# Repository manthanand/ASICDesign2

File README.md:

# ASIC Design 2 - Validation of 128-Bit AES Core

## AES Test Board
This folder contains the KiCAD project files for the board that houses the testbench for the AES Core. It mates with a BASYS 3 ARTIX 7 FPGA Board that is used to stimulate the AES
core with input signals. The following is a list of the pins and what they connect to on the FPGA:
| BASYS 3 Board Pin | AES Core PIN | 
|-------------------|--------------|
|        JB1        |      CLK     |
|        JB2        |      SE      |
|        JB3        |      EN      |
|        JB4        |     KRDY     |
|        JB7        |      SI      |
|        JB8        |     SCLK     |
|        JB9        |      SU      |
|        JB10       |     RSTN     |
|        JC7        |     DRDY     |
|        JC8        |      SO      |
|        JC9        |      BSY     |

`AES Board J3`: The following pin is used to bypass the LDO output to allow for testing with different operating voltages. If jumpered, it will use the LDO output. In order to 
replace with a power supply, remove the jumper, place `V+` of the PSU on the bottom pin and `V-` of the PSU on the `VSS1` testpoint.

## AES Test & Emulation

This folder contains the Vivado project with the testbench and emulation project files. The project is structured such that both modules are in the same project, but one can 
be set as the top module and compiled into a bitstream. That way the same project can be used for both purposes. However, since the emulation did not work when separated onto 
2 boards, this project has now been centered around just the FPGA stimuli into the PCB.

## Scripts

During the course of our debugging, we realized that the scan chains within our core were reordered before tapeout. This meant that we had to parse through the final PNR Signoff
from last semester and recreate the verilog that we emulated this semester to accurately test our scan chain. This folder houses the scripts to automatically generate the verilog
that is necessary to reorder the scan chains for sending data in and out of the core.

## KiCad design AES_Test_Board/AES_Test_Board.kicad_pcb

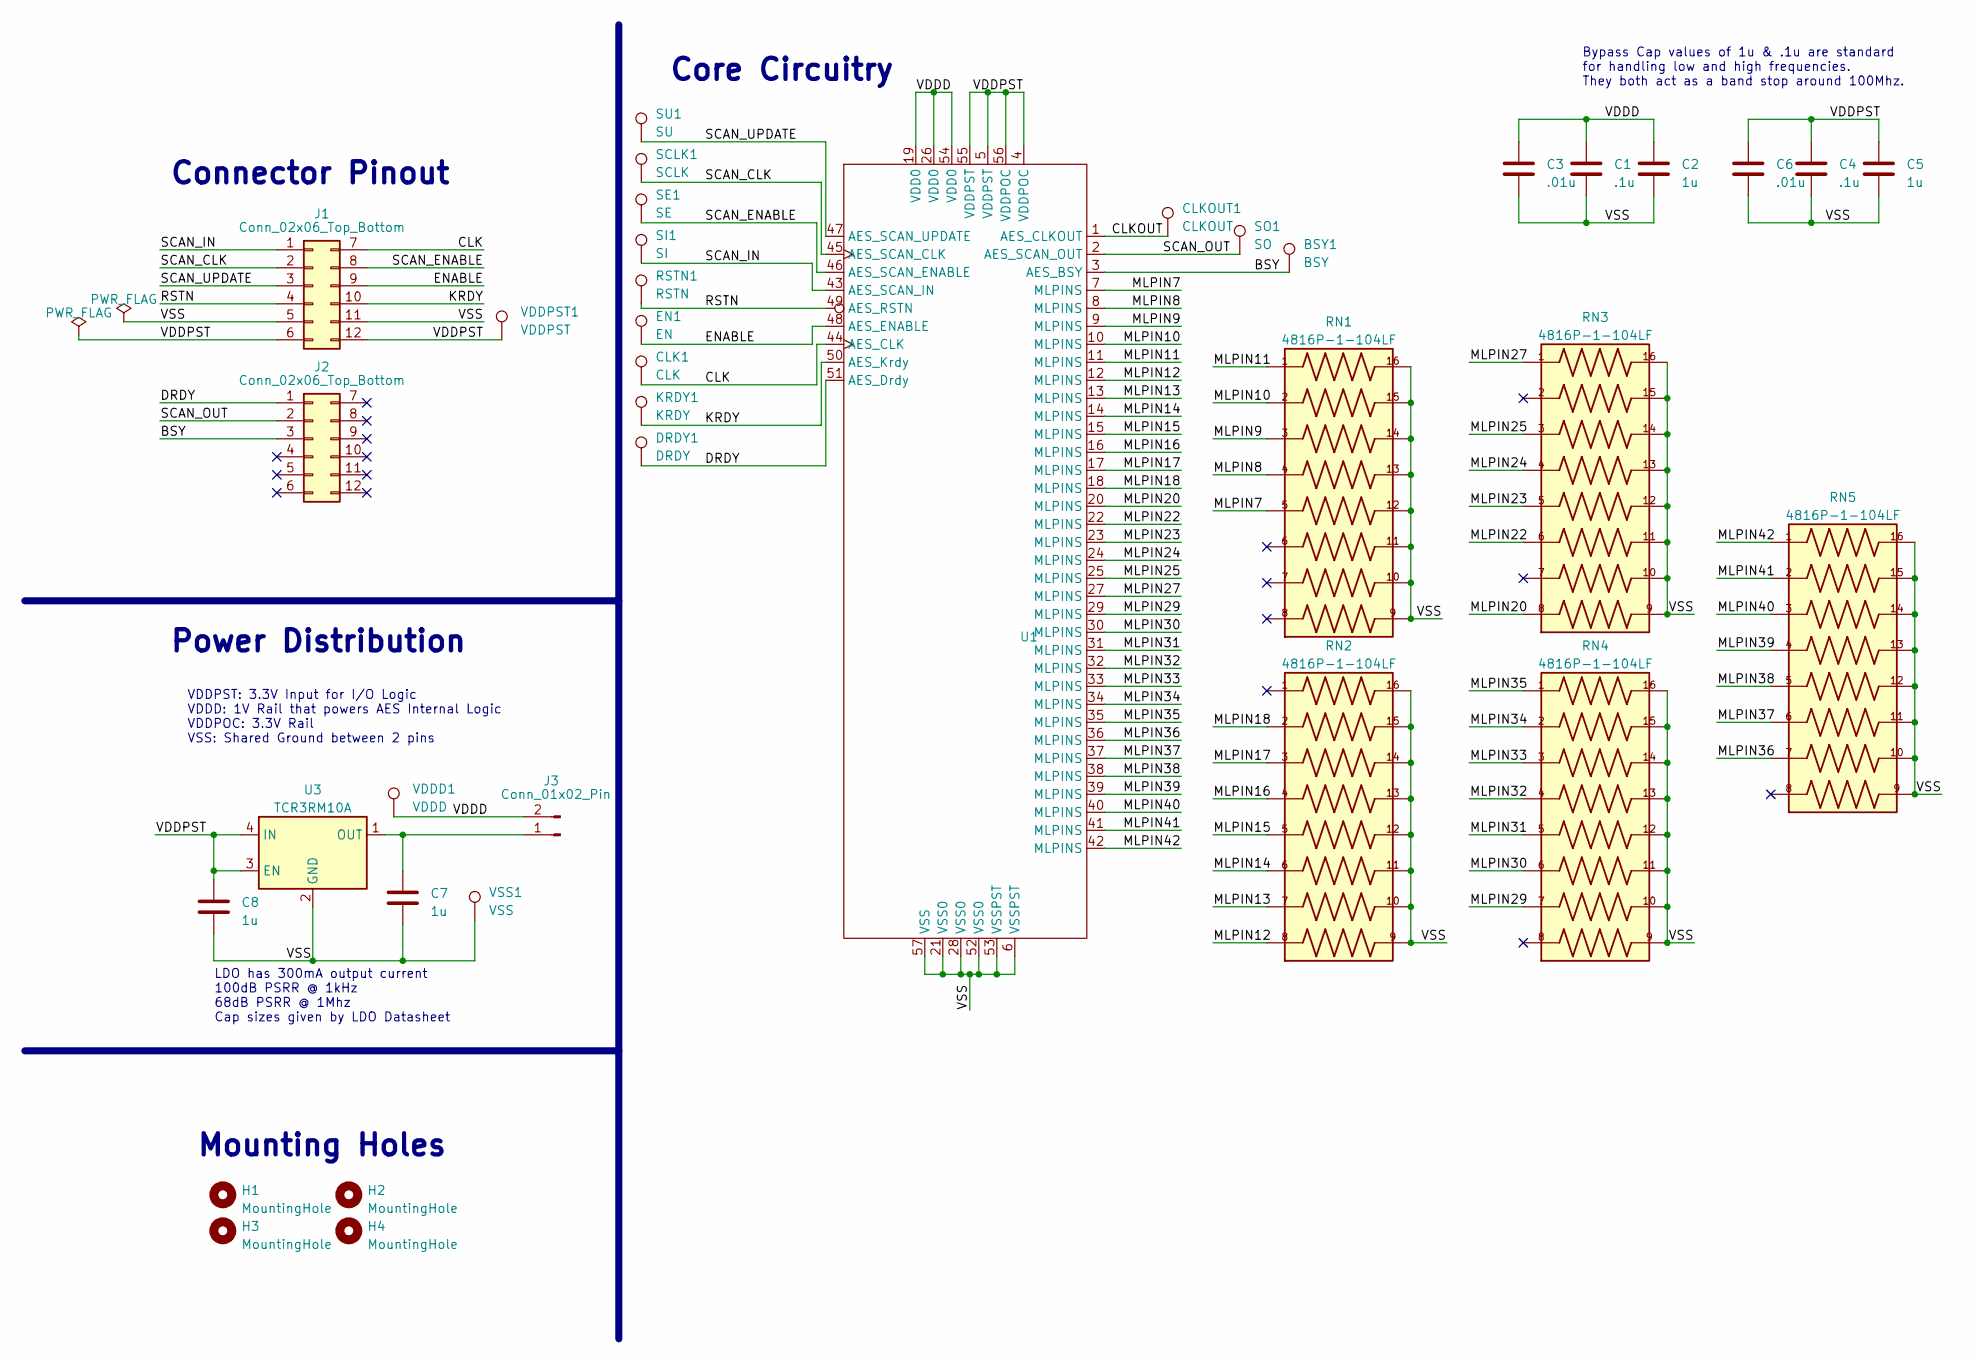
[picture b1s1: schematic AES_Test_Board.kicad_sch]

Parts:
BSY1: BSY; TestPoint_Keystone_5000-5004_Miniature
C1, C4: .1u; C_0603_1608Metric_Pad1.08x0.95mm_HandSolder
C2, C5, C7, C8: 1u; C_0603_1608Metric_Pad1.08x0.95mm_HandSolder
C3, C6: .01u; C_0603_1608Metric_Pad1.08x0.95mm_HandSolder
CLK1: CLK; TestPoint_Keystone_5000-5004_Miniature
CLKOUT1: CLKOUT; TestPoint_Keystone_5000-5004_Miniature
DRDY1: DRDY; TestPoint_Keystone_5000-5004_Miniature
EN1: EN; TestPoint_Keystone_5000-5004_Miniature
H1, H2, H3, H4: MountingHole; MountingHole_3.2mm_M3
J1, J2: Conn_02x06_Top_Bottom; pmod_pin_array_6x2_xadc
J3: Conn_01x02_Pin; PinSocket_1x02_P2.54mm_Vertical
KRDY1: KRDY; TestPoint_Keystone_5000-5004_Miniature
RN1, RN2, RN3, RN4, RN5: 4816P-1-104LF; SOIC127P762X240-16N
RSTN1: RSTN; TestPoint_Keystone_5000-5004_Miniature
SCLK1: SCLK; TestPoint_Keystone_5000-5004_Miniature
SE1: SE; TestPoint_Keystone_5000-5004_Miniature
SI1: SI; TestPoint_Keystone_5000-5004_Miniature
SO1: SO; TestPoint_Keystone_5000-5004_Miniature
SU1: SU; TestPoint_Keystone_5000-5004_Miniature
U1: QFN-56-1EP_8x8mm_P0.5mm_EP5.9x5.9mm
U3: TCR3RM10A; UDFN-4-1EP_1x1mm_P0.65mm_EP0.48x0.48mm
VDDD1: VDDD; TestPoint_Keystone_5000-5004_Miniature
VDDPST1: VDDPST; TestPoint_Keystone_5000-5004_Miniature
VSS1: VSS; TestPoint_Keystone_5000-5004_Miniature

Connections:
/BSY: BSY1.1, J2.3, U1.3 (AES_BSY)
/CLK: CLK1.1, J1.7, U1.44 (AES_CLK)
/CLKOUT: CLKOUT1.1, U1.1 (AES_CLKOUT)
/DRDY: DRDY1.1, J2.1, U1.51 (AES_Drdy)
/ENABLE: EN1.1, J1.9, U1.48 (AES_ENABLE)
/KRDY: J1.10, KRDY1.1, U1.50 (AES_Krdy)
/MLPIN7: RN1.5, U1.7 (MLPINS)
/MLPIN8: RN1.4, U1.8 (MLPINS)
/MLPIN9: RN1.3, U1.9 (MLPINS)
/MLPIN10: RN1.2, U1.10 (MLPINS)
/MLPIN11: RN1.1, U1.11 (MLPINS)
/MLPIN12: RN2.8, U1.12 (MLPINS)
/MLPIN13: RN2.7, U1.13 (MLPINS)
/MLPIN14: RN2.6, U1.14 (MLPINS)
/MLPIN15: RN2.5, U1.15 (MLPINS)
/MLPIN16: RN2.4, U1.16 (MLPINS)
/MLPIN17: RN2.3, U1.17 (MLPINS)
/MLPIN18: RN2.2, U1.18 (MLPINS)
/MLPIN20: RN3.8, U1.20 (MLPINS)
/MLPIN22: RN3.6, U1.22 (MLPINS)
/MLPIN23: RN3.5, U1.23 (MLPINS)
/MLPIN24: RN3.4, U1.24 (MLPINS)
/MLPIN25: RN3.3, U1.25 (MLPINS)
/MLPIN27: RN3.1, U1.27 (MLPINS)
/MLPIN29: RN4.7, U1.29 (MLPINS)
/MLPIN30: RN4.6, U1.30 (MLPINS)
/MLPIN31: RN4.5, U1.31 (MLPINS)
/MLPIN32: RN4.4, U1.32 (MLPINS)
/MLPIN33: RN4.3, U1.33 (MLPINS)
/MLPIN34: RN4.2, U1.34 (MLPINS)
/MLPIN35: RN4.1, U1.35 (MLPINS)
/MLPIN36: RN5.7, U1.36 (MLPINS)
/MLPIN37: RN5.6, U1.37 (MLPINS)
/MLPIN38: RN5.5, U1.38 (MLPINS)
/MLPIN39: RN5.4, U1.39 (MLPINS)
/MLPIN40: RN5.3, U1.40 (MLPINS)
/MLPIN41: RN5.2, U1.41 (MLPINS)
/MLPIN42: RN5.1, U1.42 (MLPINS)
/RSTN: J1.4, RSTN1.1, U1.49 (AES_RSTN)
/SCAN_CLK: J1.2, SCLK1.1, U1.45 (AES_SCAN_CLK)
/SCAN_ENABLE: J1.8, SE1.1, U1.46 (AES_SCAN_ENABLE)
/SCAN_IN: J1.1, SI1.1, U1.43 (AES_SCAN_IN)
/SCAN_OUT: J2.2, SO1.1, U1.2 (AES_SCAN_OUT)
/SCAN_UPDATE: J1.3, SU1.1, U1.47 (AES_SCAN_UPDATE)
/VDDD: C1.1, C2.1, C3.1, J3.2, U1.19 (VDD0), U1.26 (VDD0), U1.54 (VDD0), VDDD1.1
/VDDPST: C4.1, C5.1, C6.1, C8.1, J1.6, J1.12, U1.4 (VDDPOC), U1.5 (VDDPST), U1.55 (VDDPST), U1.56 (VDDPOC), U3.3 (EN), U3.4 (IN), VDDPST1.1
/VSS: C1.2, C2.2, C3.2, C4.2, C5.2, C6.2, C7.2, C8.2, J1.5, J1.11, RN1.9, RN1.10, RN1.11, RN1.12, RN1.13, RN1.14, RN1.15, RN1.16, RN2.9, RN2.10, RN2.11, RN2.12, RN2.13, RN2.14, RN2.15, RN2.16, RN3.9, RN3.10, RN3.11, RN3.12, RN3.13, RN3.14, RN3.15, RN3.16, RN4.9, RN4.10, RN4.11, RN4.12, RN4.13, RN4.14, RN4.15, RN4.16, RN5.9, RN5.10, RN5.11, RN5.12, RN5.13, RN5.14, RN5.15, RN5.16, U1.6 (VSSPST), U1.21 (VSS0), U1.28 (VSS0), U1.52 (VSS0), U1.53 (VSSPST), U1.57 (VSS), U3.2 (GND), U3.5 (GND), VSS1.1
unnamed: C7.1, J3.1, U3.1 (OUT)

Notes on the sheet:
LDO has 300mA output current 100dB PSRR @ 1kHz 68dB PSRR @ 1Mhz Cap sizes given by LDO Datasheet
Power Distribution
Core Circuitry
Bypass Cap values of 1u & .1u are standard for handling low and high frequencies. They both act as a band stop around 100Mhz.
Mounting Holes
VDDPST: 3.3V Input for I/O Logic VDDD: 1V Rail that powers AES Internal Logic VDDPOC: 3.3V Rail VSS: Shared Ground between 2 pins
Connector Pinout

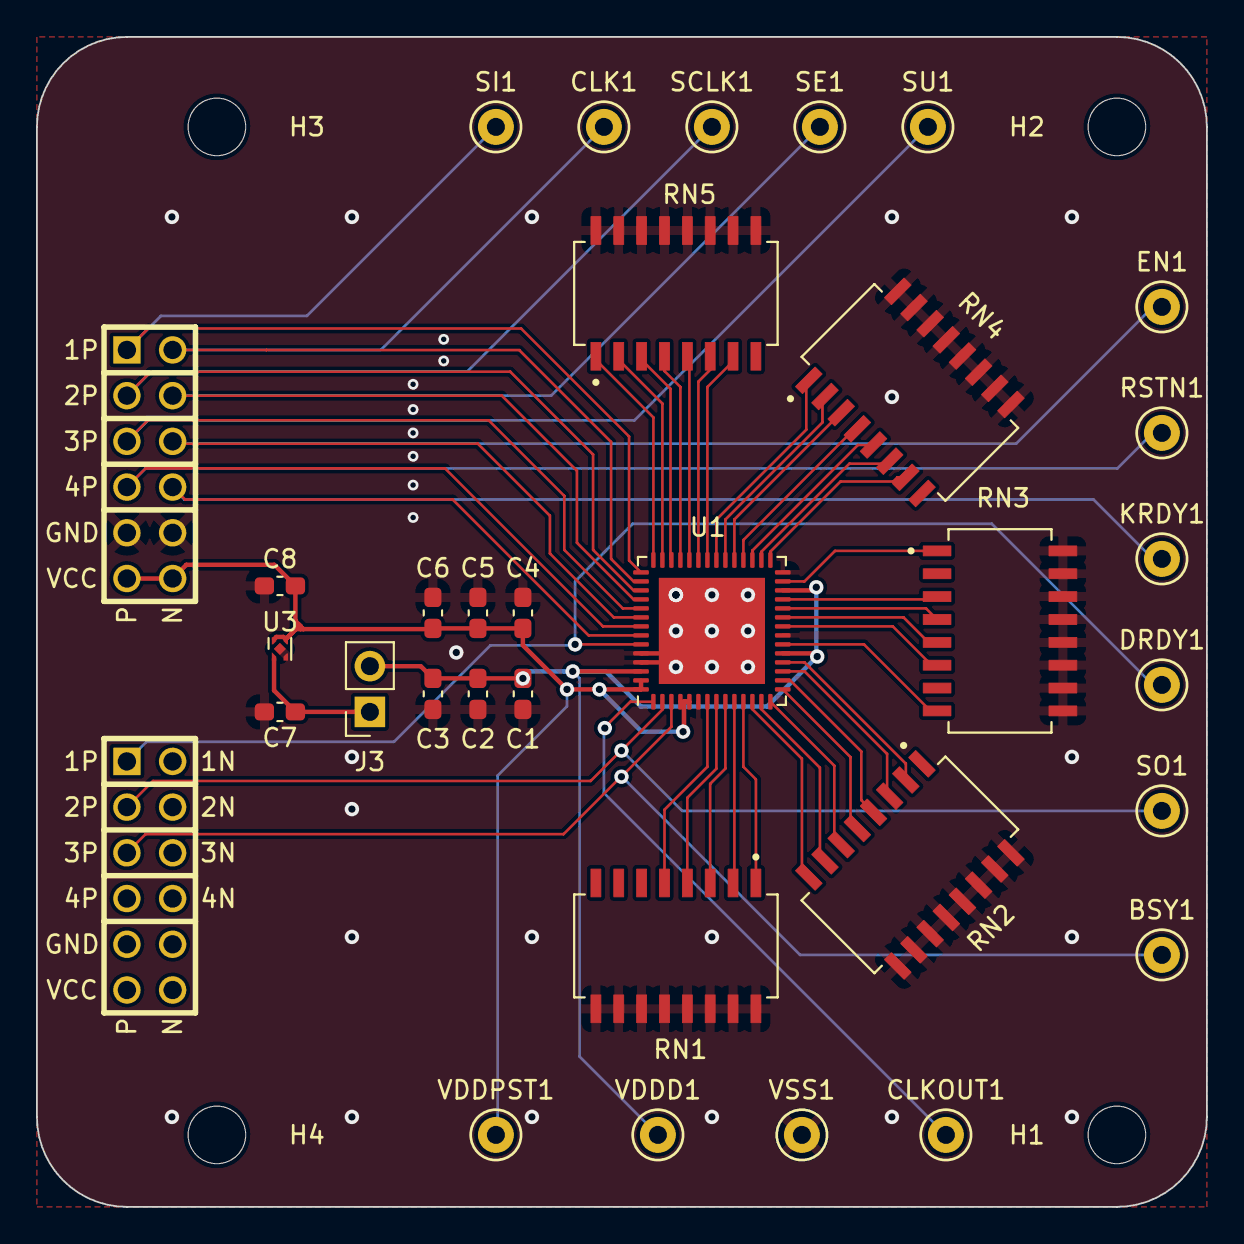
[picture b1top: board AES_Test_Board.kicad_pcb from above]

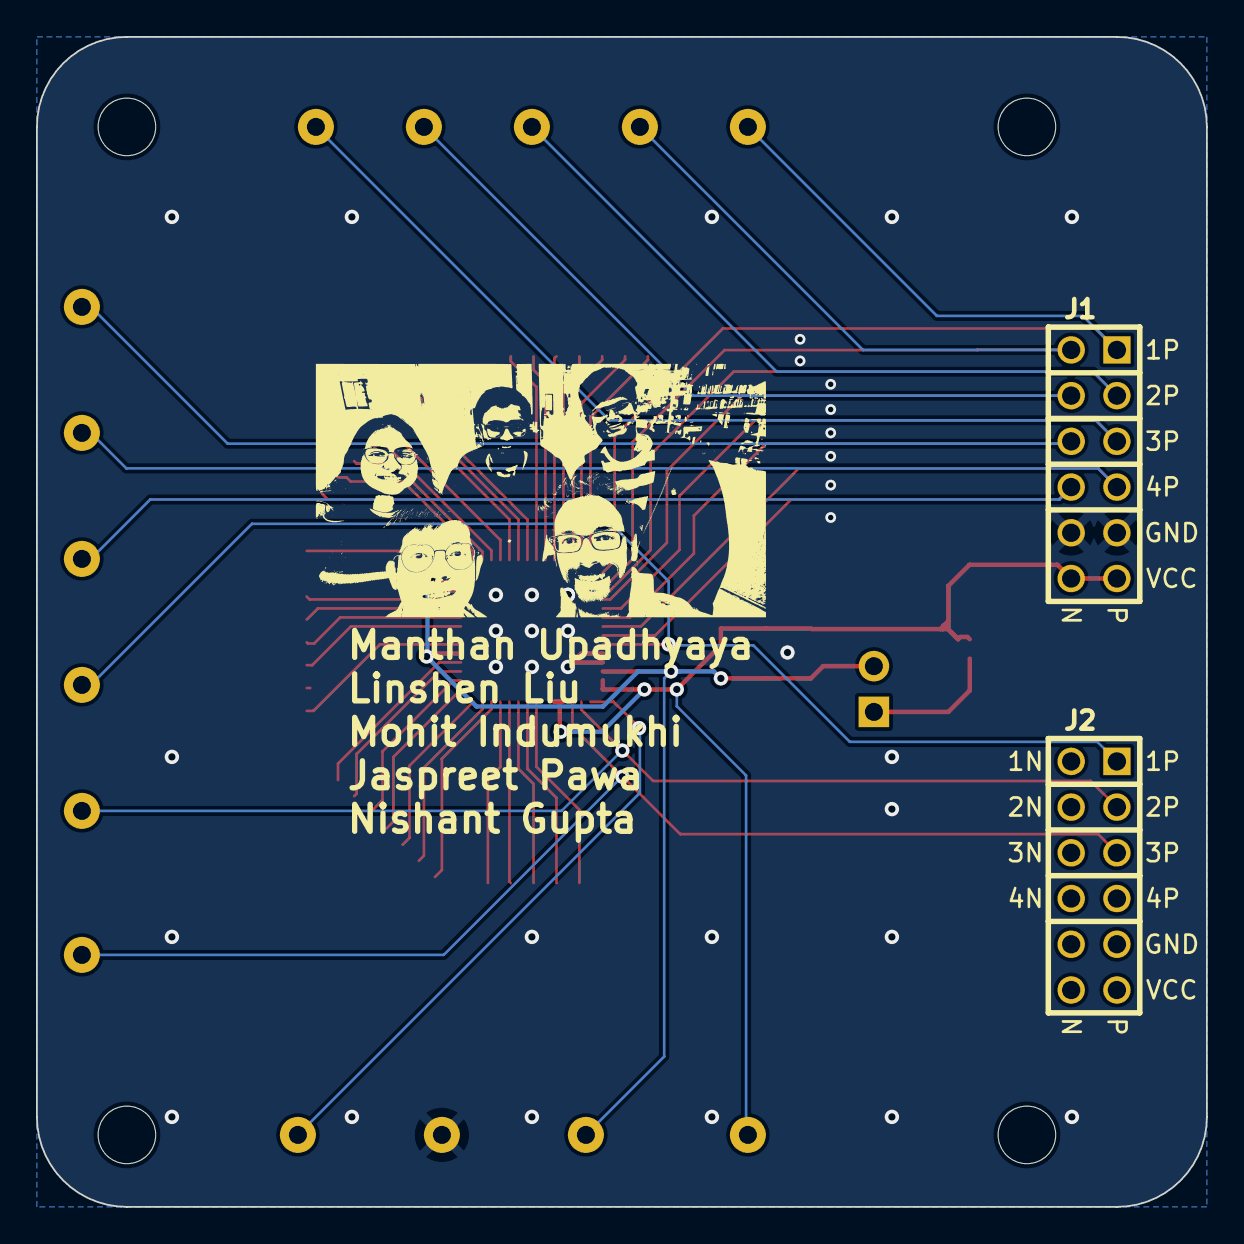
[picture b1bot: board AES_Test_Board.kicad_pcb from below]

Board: 2 copper layers, 65.0 x 65.0 mm, 37 parts (2 on the bottom side), 48 nets.

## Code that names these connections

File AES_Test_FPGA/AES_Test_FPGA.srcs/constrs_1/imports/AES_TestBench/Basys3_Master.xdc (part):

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    
##Pmod Header JB
##Sch name = JB1
set_property PACKAGE_PIN A14 [get_ports {BSY}]          
    set_property IOSTANDARD LVCMOS33 [get_ports {BSY}]
#Sch name = JB2
set_property PACKAGE_PIN A16 [get_ports {KRDY}]                 
    set_property IOSTANDARD LVCMOS33 [get_ports {KRDY}]
#Sch name = JB3
set_property PACKAGE_PIN B15 [get_ports {EN}]                   
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set_property PACKAGE_PIN B16 [get_ports {SI}]                   
    set_property IOSTANDARD LVCMOS33 [get_ports {SI}]
#Sch name = JB7
set_property PACKAGE_PIN A15 [get_ports {DRDY}]                 
    set_property IOSTANDARD LVCMOS33 [get_ports {DRDY}]
#Sch name = JB8
set_property PACKAGE_PIN A17 [get_ports {CLK}]                  
    set_property IOSTANDARD LVCMOS33 [get_ports {CLK}]
set_property CLOCK_DEDICATED_ROUTE FALSE [get_nets {CLK_IBUF}]
#Sch name = JB9
set_property PACKAGE_PIN C15 [get_ports {RSTN}]                 
    set_property IOSTANDARD LVCMOS33 [get_ports {RSTN}]
#Sch name = JB10 
set_property PACKAGE_PIN C16 [get_ports {SE}]                   
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set_property PACKAGE_PIN N17 [get_ports {SU}]                   
    set_property IOSTANDARD LVCMOS33 [get_ports {SU}]
#Sch name = JC4
#set_property PACKAGE_PIN P18 [get_ports {CLKOUT}]                   
#    set_property IOSTANDARD LVCMOS33 [get_ports {CLKOUT}]
##Sch name = JC7
#set_property PACKAGE_PIN L17 [get_ports {JC[4]}]                   
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
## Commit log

2024-01-25 Added vivado and kicad project files
2024-01-25 Used right connector
2024-01-26 FPGA Emulation works
2024-01-29 Changed structure to have better names. 2 vivado projects - 1 for test device and one for emulation device
2024-02-05 Finished board
2024-02-07 Emulation Board bitstream works
2024-02-09 Added file as design source and converted to verilog
2024-02-15 Created new vivado project that has both test and emulation synthesizable code within it. Also changed PCB to match professors input
2024-02-16 Combined fpga works
2024-02-22 Added 3 capacitors per power rail and changed pads to 0603
2024-02-25 Created Bitstreams for both FPGA's
2024-02-27 Added Power measurement circuitry and regenerated gerbers
2024-03-06 Fixed board to match pinout
2024-03-06 Added power pins to connection
2024-03-06 Fixed zip file
2024-03-18 works nowA
2024-03-20 Changed code to run tests multiple times
2024-04-01 Added UART. untested
2024-04-09 Tested with actual board
2024-04-12 Removed unnecessary projects and added scan chain reordering to emulation
2024-04-12 Updated scripts to write to file
2024-04-12 Simulation definitely works
2024-04-15 EVERYTHING WORKS
2024-04-15 Added variable clock divider
2024-04-15 added rst button
2024-04-16 testing push
2024-04-17 Added clocking wizard
2024-04-17 tried to fix clocking wizard issue
2024-04-18 Added more frequencies for testing
2024-04-19 Added clocking wizard. Leads to timing violations
2024-04-19 Clocks that barely miss timing violations
